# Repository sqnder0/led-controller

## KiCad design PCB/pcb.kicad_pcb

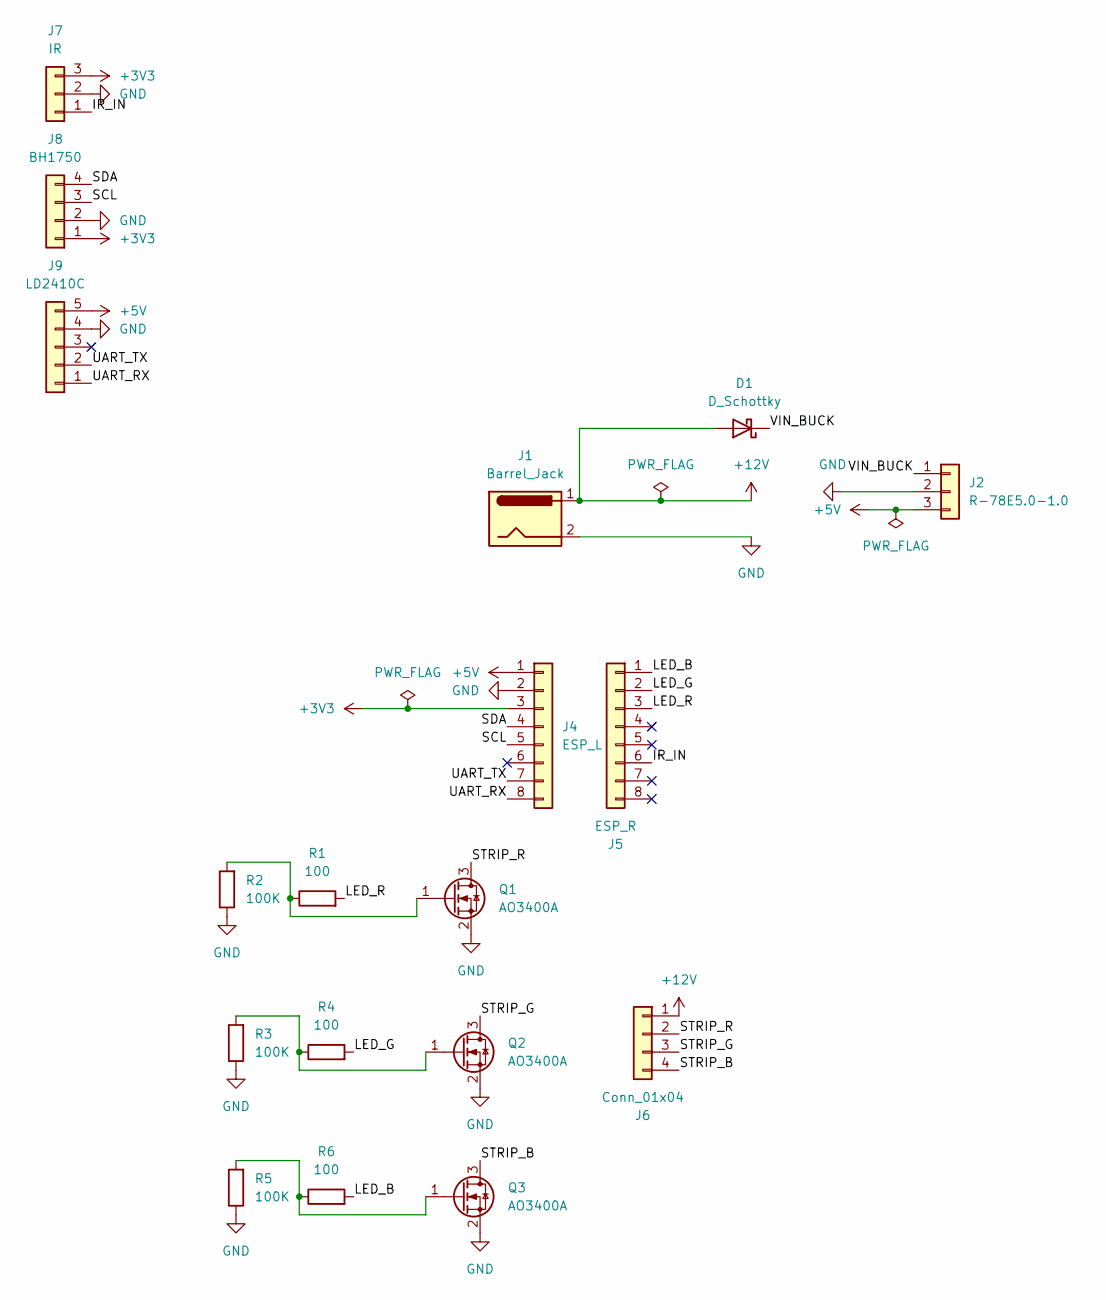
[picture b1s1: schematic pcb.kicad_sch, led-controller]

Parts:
D1: D_Schottky; D_SMA
J1: Barrel_Jack; BarrelJack_Horizontal
J2: R-78E5.0-1.0; PinHeader_1x03_P2.54mm_Vertical
J4: ESP_L; PinSocket_1x08_P2.54mm_Vertical
J5: ESP_R; PinSocket_1x08_P2.54mm_Vertical
J6: Conn_01x04; TerminalBlock_Phoenix_MKDS-1,5-4-5.08_1x04_P5.08mm_Horizont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
J7: IR; PinHeader_1x03_P2.54mm_Vertical
J8: BH1750; PinSocket_1x04_P2.54mm_Vertical
J9: LD2410C; PinSocket_1x05_P1.27mm_Vertical
Q1, Q2, Q3: AO3400A; SOT-23
R1, R4, R6: 100; R_0805_2012Metric
R2, R3, R5: 100K; R_0805_2012Metric

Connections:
+3V3: J4.3, J7.3, J8.1
+5V: J2.3, J4.1, J9.5
+12V: D1.2 (A), J1.1, J6.1
/IR_IN: J5.6, J7.1
/LED_B: J5.1, R6.2
/LED_G: J5.2, R4.2
/LED_R: J5.3, R1.2
/SCL: J4.5, J8.3
/SDA: J4.4, J8.4
/STRIP_B: J6.4, Q3.3 (D)
/STRIP_G: J6.3, Q2.3 (D)
/STRIP_R: J6.2, Q1.3 (D)
/UART_RX: J4.8, J9.1
/UART_TX: J4.7, J9.2
/VIN_BUCK: D1.1 (K), J2.1
GND: J1.2, J2.2, J4.2, J7.2, J8.2, J9.4, Q1.2 (S), Q2.2 (S), Q3.2 (S), R2.1, R3.1, R5.1
unnamed: Q1.1 (G), R1.1, R2.2
unnamed: Q2.1 (G), R3.2, R4.1
unnamed: Q3.1 (G), R5.2, R6.1

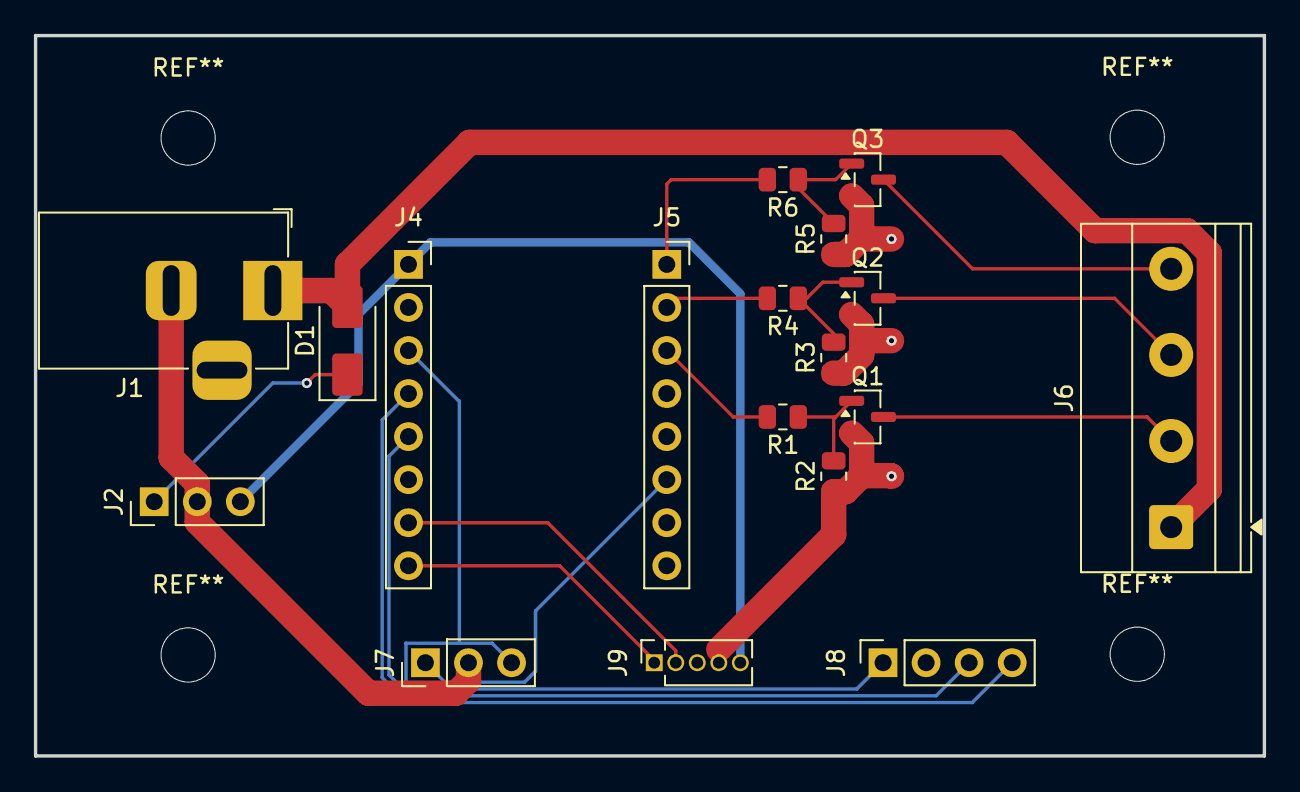
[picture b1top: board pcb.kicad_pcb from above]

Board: 2 copper layers, 72.5 x 42.5 mm, 18 parts (0 on the bottom side), 19 nets.
